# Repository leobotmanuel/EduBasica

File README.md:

# EduBasica

EDUBASICA es una tarjeta de prototipado rápido para conectar a Arduino. Incluye componentes electrónicos básicos para gran variedad de prácticas y proyectos. Es una tarjeta multipropósito con componentes electrónicos incluidos que puedes usar para fabricar un robot, controlar un sistema de poleas, activar barreras, comunicar dispositivos bluetooth, y todo lo que te puedas imaginar.

 www.arduino.org -- www.arduino.cc

 EduBasica -- www.practicasconarduino.com

# Conexiones EduBasica con Arduino

# Prácticas de programación y electrónica 
# con Arduino-EduBasica

Archivo en pdf de 4ºESO

https://www.dropbox.com/s/mtubbro328of7fd/PracticasConArduino2-2.pdf?dl=0
# Autores
Pablo E. García -- https://www.linkedin.com/in/pablo-evaristo-garc%C3%ADa-palacios-083a5483

Manuel Hidalgo -- https://es.linkedin.com/in/manuel-hidalgo-díaz-b95b467b

Jorge Luis Loza -- https://es.linkedin.com/in/jorgeluisloza

Jorge Muñoz -- https://es.linkedin.com/in/jorge-mu%C3%B1oz-8a641160/es

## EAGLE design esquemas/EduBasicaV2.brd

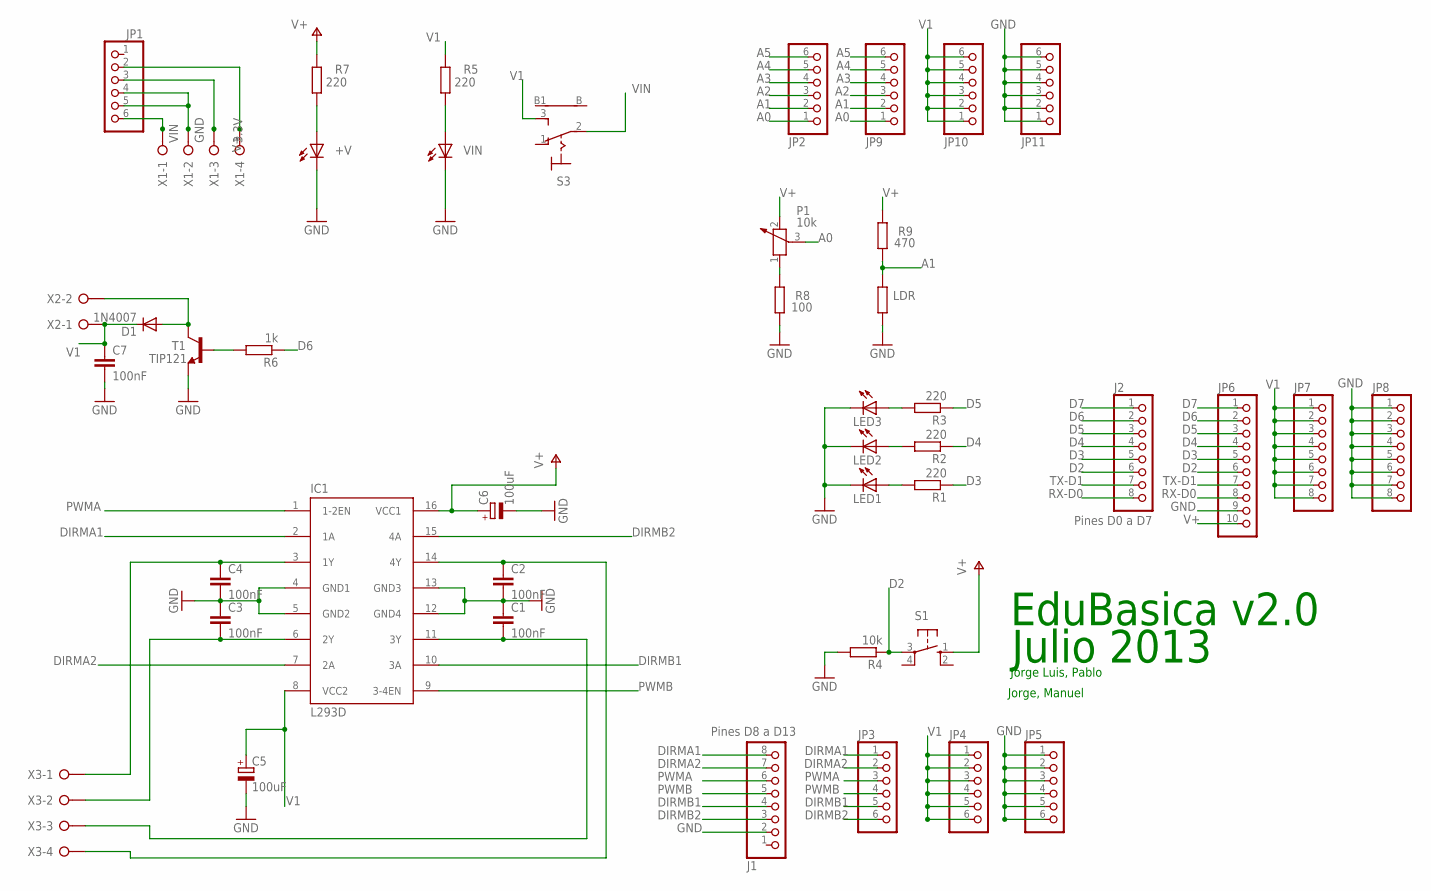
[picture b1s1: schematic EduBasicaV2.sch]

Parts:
+V: LED3MM
C1, C2, C3, C4, C7: 100nF; C5B5.5
C5, C6: 100uF; E2,5-5
D1: 1N4007; D-7.5
IC1: L293D; DIL16
J1: Pines D8 a D13; 1X08
J2: Pines D0 a D7; 1X08
JP1, JP2, JP3, JP4, JP5, JP9, JP10, JP11: PINHD-1X6; 1X06
JP6: PINHD-1X10; 1X10
JP7, JP8: PINHD-1X8; 1X08
LDR: R-EU_0204/2V; 0204V
LED1, LED2, LED3: LED5MM
P1: 10k; PT-10
R1, R2, R3, R5, R7: 220; 0204/7
R4: 10k; 0204/7
R6: 1k; 0204/7
R8: 100; 0204/7
R9: 470; 0204/7
S1: 10-XX; B3F-10XX
S3: 9070-1W
T1: TIP121; TO220V
VIN: LED3MM
X1, X3: W237-04P; W237-4P
X2: W237-02P; W237-132

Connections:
3.3V: JP1.2, X1.4
A0: JP2.1, JP9.1, P1.3
A1: JP2.2, JP9.2, LDR.2, R9.1
A2: JP2.3, JP9.3
A3: JP2.4, JP9.4
A4: JP2.5, JP9.5
A5: JP2.6, JP9.6
D2: J2.6, JP6.6, R4.1, S1.3
D3: J2.5, JP6.5, R1.1
D4: J2.4, JP6.4, R2.1
D5: J2.3, JP6.3, R3.1
D6: J2.2, JP6.2, R6.1
D7: J2.1, JP6.1
DIRMA1: IC1.2 (1A), J1.8, JP3.1
DIRMA2: IC1.7 (2A), J1.7, JP3.2
DIRMB1: IC1.10 (3A), J1.4, JP3.5
DIRMB2: IC1.15 (4A), J1.3, JP3.6
GND: +V.K (C), C1.1, C2.2, C3.1, C4.2, C5.-, C6.-, C7.2, IC1.4 (GND1), IC1.5 (GND2), IC1.12 (GND4), IC1.13 (GND3), J1.2, JP1.4, JP1.5, JP5.1, JP5.2, JP5.3, JP5.4, JP5.5, JP5.6, JP6.9, JP8.1, JP8.2, JP8.3, JP8.4, JP8.5, JP8.6, JP8.7, JP8.8, JP11.1, JP11.2, JP11.3, JP11.4, JP11.5, JP11.6, LDR.1, LED1.K (C), LED2.K (C), LED3.K (C), R4.2, R8.1, T1.3 (E), VIN.K (C), X1.2
unnamed: R6.2, T1.1 (B)
unnamed: D1.A, T1.2 (C), X2.2
unnamed: P1.1, R8.2
unnamed: R5.1, VIN.A
unnamed: LED3.A, R3.2
unnamed: LED2.A, R2.2
unnamed: LED1.A, R1.2
unnamed: C4.1, IC1.3 (1Y), X3.1
unnamed: C3.2, IC1.6 (2Y), X3.2
unnamed: C1.2, IC1.11 (3Y), X3.3
unnamed: C2.1, IC1.14 (4Y), X3.4
unnamed: +V.A, R7.1
PWMA: IC1.1 (1-2EN), J1.6, JP3.3
PWMB: IC1.9 (3-4EN), J1.5, JP3.4
RX-D0: J2.8, JP6.8
TX-D1: J2.7, JP6.7
V1: C5.+, C7.1, D1.C, IC1.8 (VCC2), JP4.1, JP4.2, JP4.3, JP4.4, JP4.5, JP4.6, JP7.1, JP7.2, JP7.3, JP7.4, JP7.5, JP7.6, JP7.8, JP10.1, JP10.2, JP10.3, JP10.4, JP10.5, JP10.6, R5.2, S3.3 (S), X2.1
V+: C6.+, IC1.16 (VCC1), JP1.3, JP6.10, P1.2, R7.2, R9.2, S1.1 (S), X1.3
VIN: JP1.6, S3.2, X1.1

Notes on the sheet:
EduBasica v2.0
Jorge Luis, Pablo
Jorge, Manuel
Julio 2013

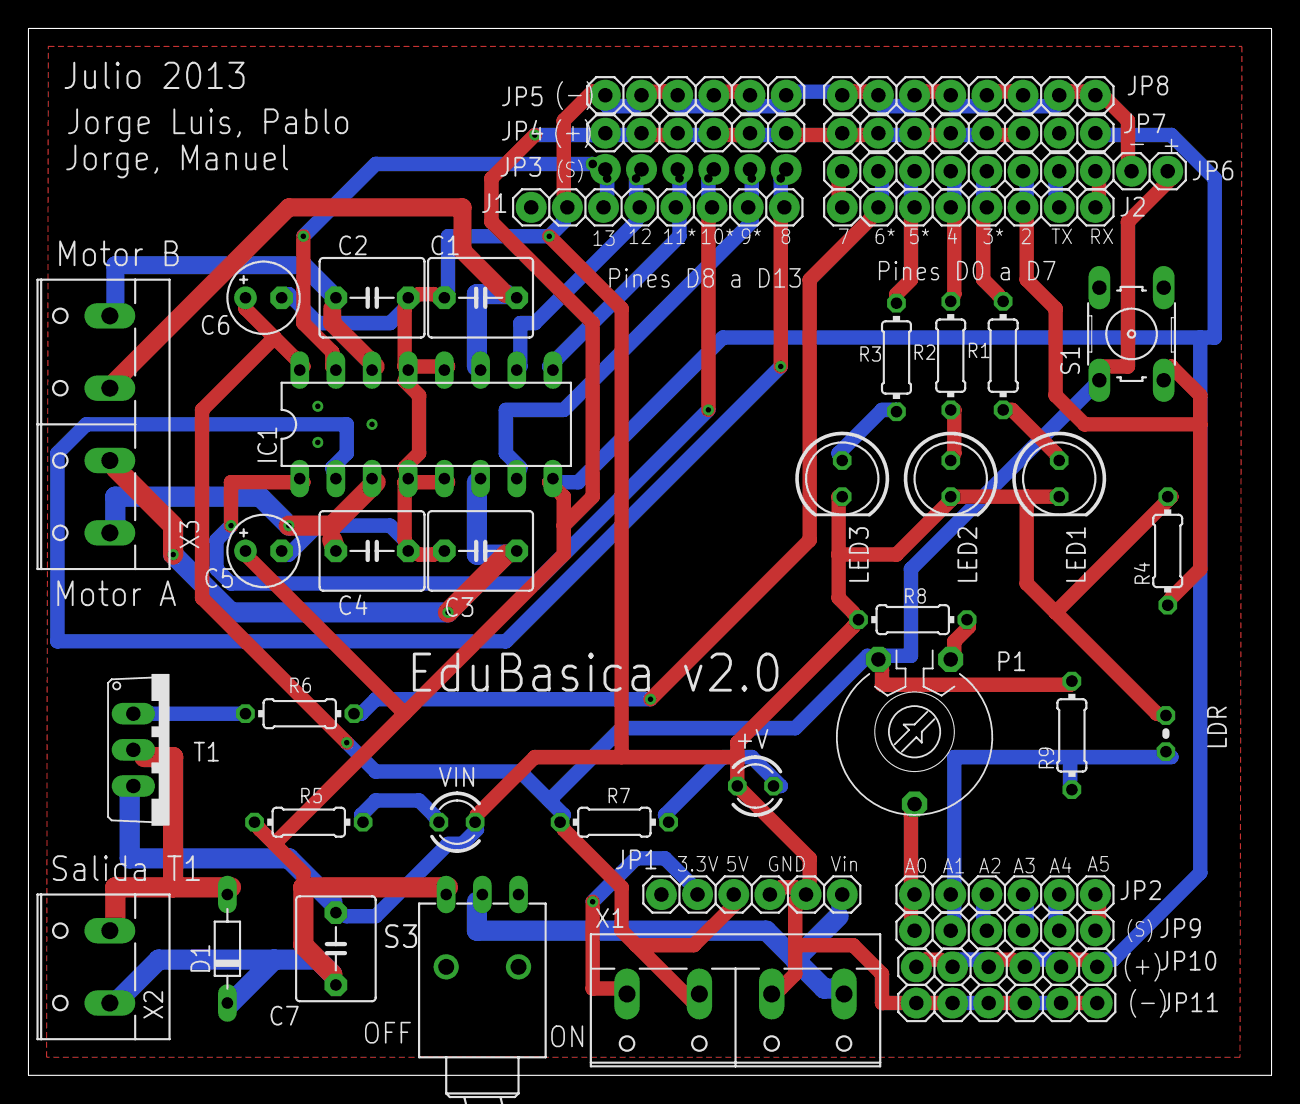
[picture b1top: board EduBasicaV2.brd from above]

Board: 2 copper layers, 87.3 x 73.5 mm, 44 parts (1 on the bottom side), 37 nets.

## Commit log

2017-11-27 Create 03_LDR
2024-07-02 Update README.md
    actualizacion readme 13:00, 02/07/2024
2024-07-28 Update README.md
    link roto
